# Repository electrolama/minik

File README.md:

# minik

A tiny RP2040 module for small embedded things!

minik is designed by Electrolama / @omerk and licensed under the Solderpad Hardware License 2.0.

## Status

module design files are already in this repo, breakout and libraries to follow. [Here's a preview](https://twitter.com/OmerK/status/1535297431444791298) of what the module and breakout looks like.

## CircuitPython support

minik is supported by CircuitPython! Grab the latest builds [here](https://adafruit-circuit-python.s3.amazonaws.com/index.html?prefix=bin/electrolama_minik).

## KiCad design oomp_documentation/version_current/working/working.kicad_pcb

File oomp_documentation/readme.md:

# None

## Description
None/
## Bill of Materials
| Id | Designator | Footprint | Quantity | Designation | Supplier and ref |  |
| --- | --- | --- | --- | --- | --- | --- |
| 1 | C4,C113,C108,C107,C1<br>09,C112,C114,C105,C1<br>11,C110,C2,C104 | _PKG_C_0402 | 12 | 100n |  |  |
| 2 | R101,R105 | _PKG_R_0402 | 2 | 10k |  |  |
| 3 | R104,R106 | _PKG_R_0402 | 2 | 1k |  |  |
| 4 | C3 | _PKG_C_0402 | 1 | 10u |  |  |
| 5 | C106,C103 | _PKG_C_0402 | 2 | 1u |  |  |
| 6 | R102,R103 | _PKG_R_0402 | 2 | 27 |  |  |
| 7 | LED1 | WS2812B-2020 | 1 | WS2812B-2020 |  |  |
| 8 | C102,C101 | _PKG_C_0402 | 2 | 12p |  |  |
| 9 | IC101 | QFN-56 | 1 | RP2040 |  |  |
| 10 | C1 | _PKG_C_0402 | 1 | 10n |  |  |
| 11 | IC102 | SON50P300X200X60-9N | 1 | MEMORY-W25Q16FWUXIE |  |  |
| 12 | XT101 | XTAL-4P-3225 | 1 | 12MHz |  |  |
| 13 | L1 | _PKG_L_0402 | 1 |  |  |  |

## Images

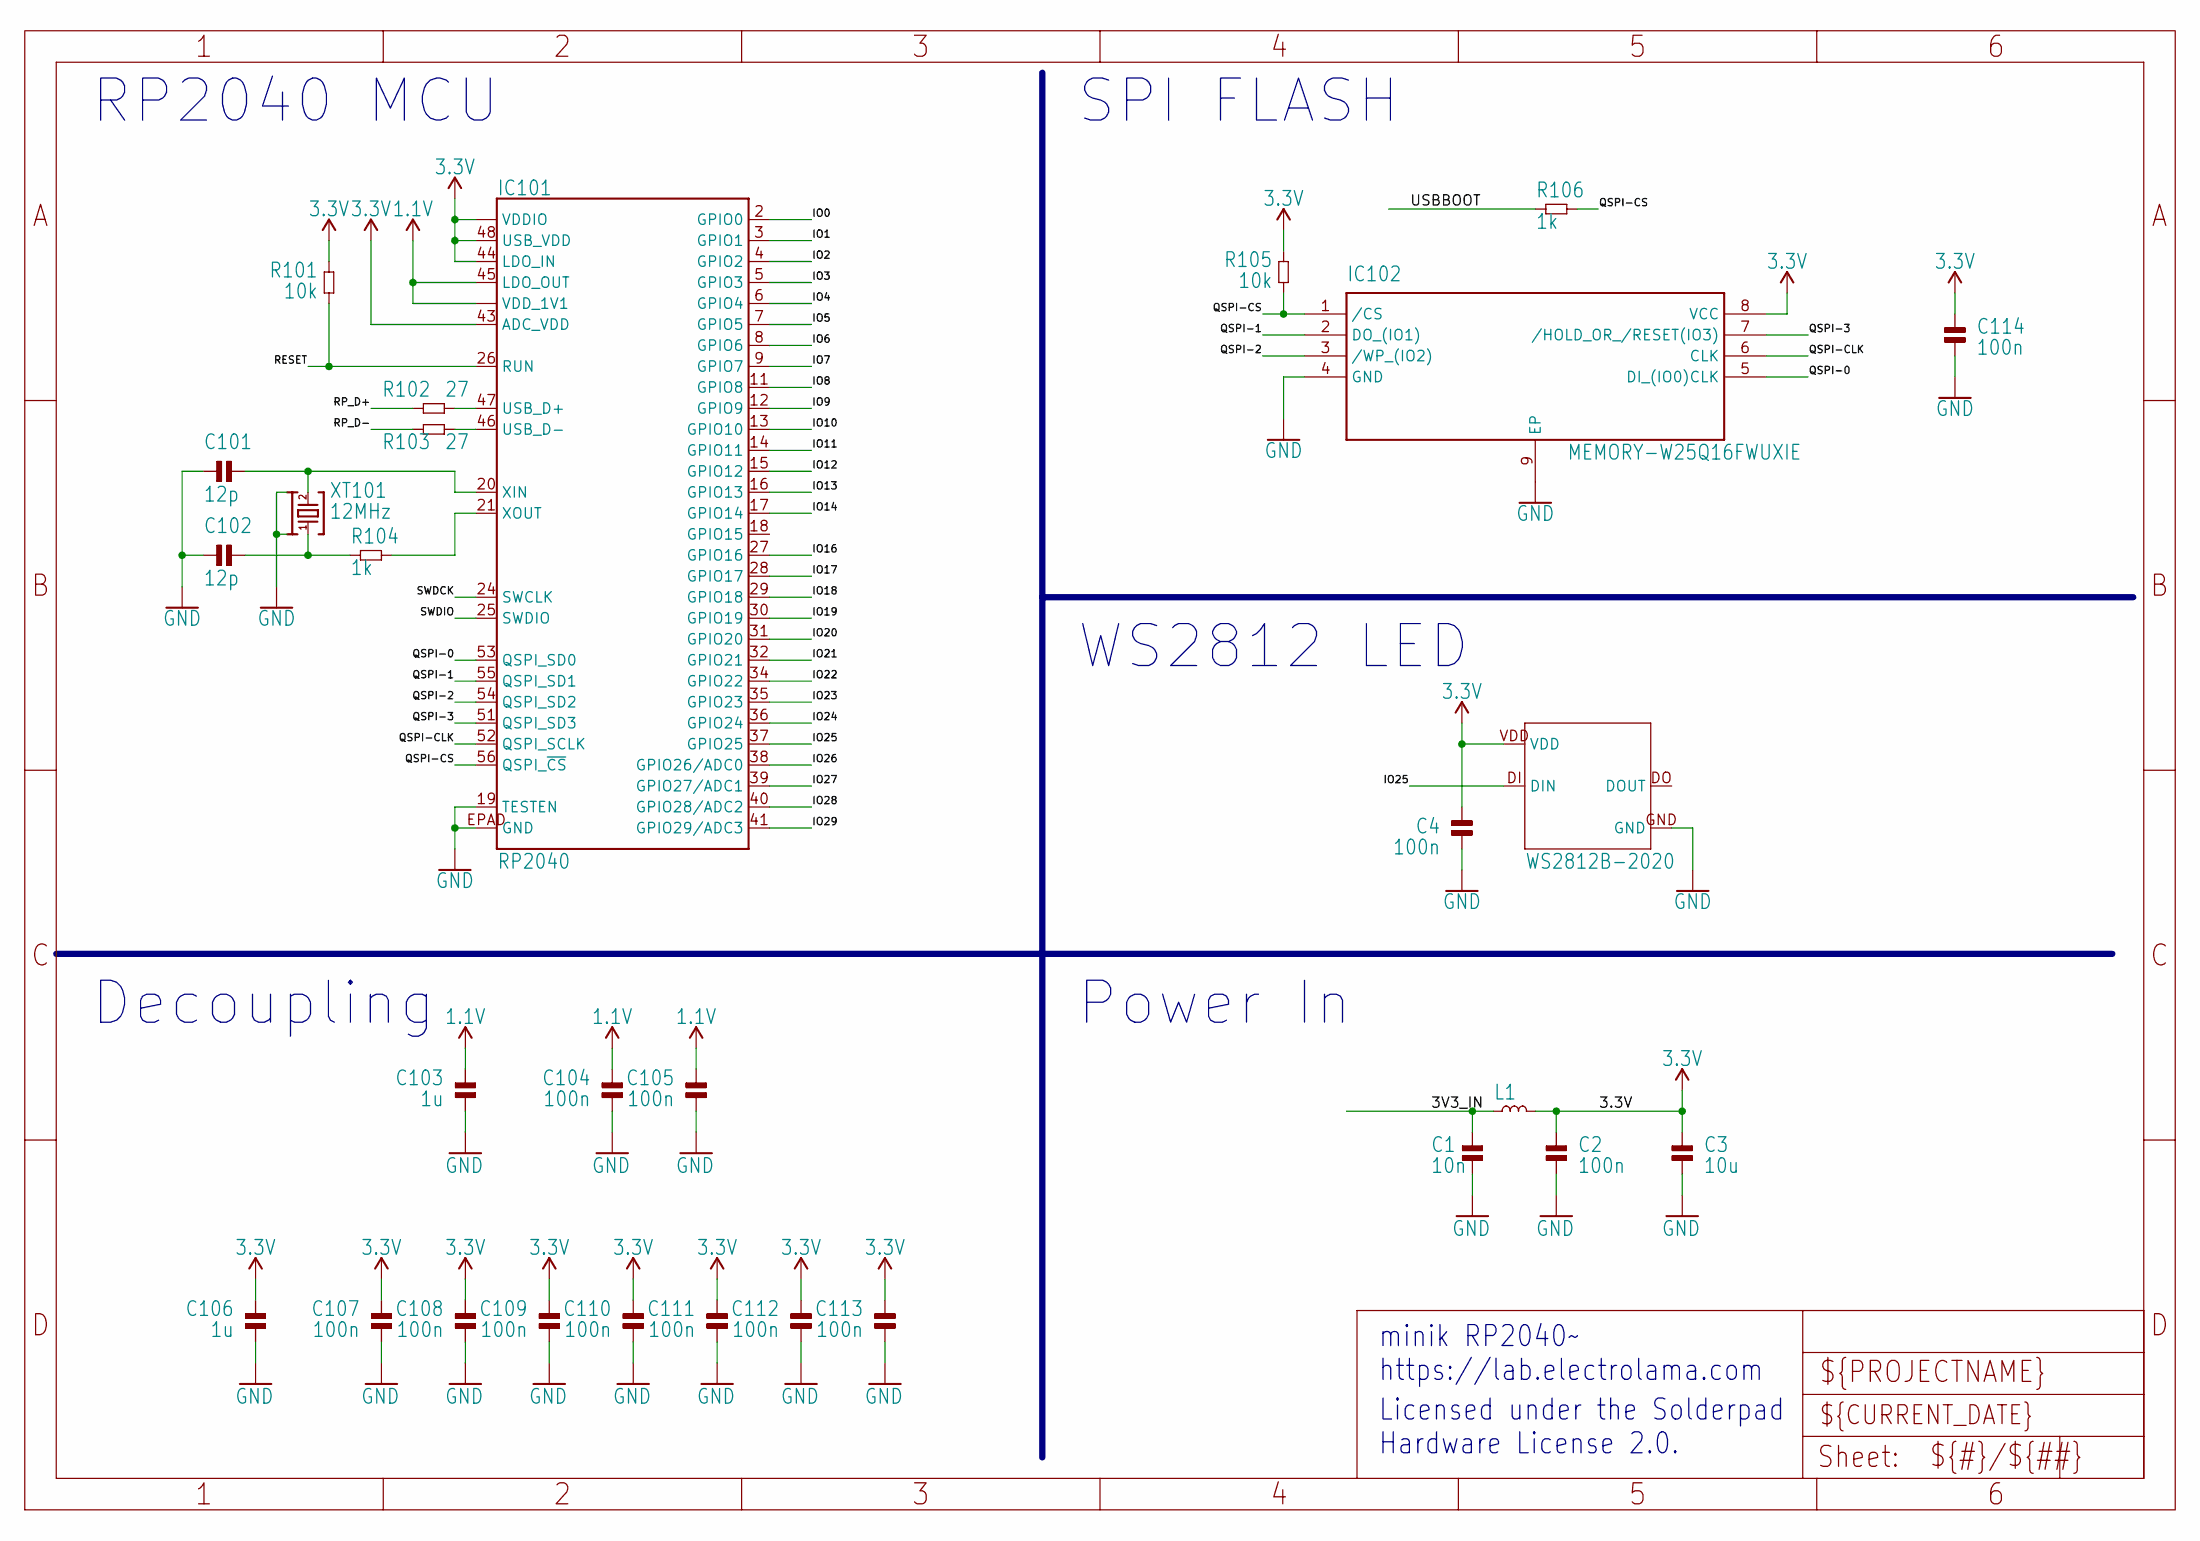
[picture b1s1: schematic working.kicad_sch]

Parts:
C1: 10n; _PKG_C_0402
C2, C4, C104, C105, C107, C108, C109, C110, C111, C112, C113, C114: 100n; _PKG_C_0402
C3: 10u; _PKG_C_0402
C101, C102: 12p; _PKG_C_0402
C103, C106: 1u; _PKG_C_0402
IC101: RP2040; QFN-56
IC102: MEMORY-W25Q16FWUXIE; SON50P300X200X60-9N
L1: INDUCTOR-0402; _PKG_L_0402
LED1: WS2812B-2020
R101, R105: 10k; _PKG_R_0402
R102, R103: 27; _PKG_R_0402
R104, R106: 1k; _PKG_R_0402
XT101: 12MHz; XTAL-4P-3225

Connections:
1.1V: C103.2, C104.2, C105.2, IC101.23 (VDD_1V1), IC101.45 (LDO_OUT), IC101.50 (VDD_1V1)
3.3V: C2.2, C3.2, C4.2, C106.2, C107.2, C108.2, C109.2, C110.2, C111.2, C112.2, C113.2, C114.2, IC101.1 (VDDIO), IC101.10 (VDDIO), IC101.22 (VDDIO), IC101.33 (VDDIO), IC101.42 (VDDIO), IC101.43 (ADC_VDD), IC101.44 (LDO_IN), IC101.48 (USB_VDD), IC101.49 (VDDIO), IC102.8 (VCC), L1.2, LED1.VDD, R101.2, R105.2
3V3_IN: C1.2, L1.1
GND: C1.1, C2.1, C3.1, C4.1, C101.1, C102.1, C103.1, C104.1, C105.1, C106.1, C107.1, C108.1, C109.1, C110.1, C111.1, C112.1, C113.1, C114.1, IC101.19 (TESTEN), IC101.EPAD (GND), IC102.4 (GND), IC102.9 (EP), LED1.GND, XT101.2, XT101.4
IO0: IC101.2 (GPIO0)
IO1: IC101.3 (GPIO1)
IO2: IC101.4 (GPIO2)
IO3: IC101.5 (GPIO3)
IO4: IC101.6 (GPIO4)
IO5: IC101.7 (GPIO5)
IO6: IC101.8 (GPIO6)
IO7: IC101.9 (GPIO7)
IO8: IC101.11 (GPIO8)
IO9: IC101.12 (GPIO9)
IO10: IC101.13 (GPIO10)
IO11: IC101.14 (GPIO11)
IO12: IC101.15 (GPIO12)
IO13: IC101.16 (GPIO13)
IO14: IC101.17 (GPIO14)
IO16: IC101.27 (GPIO16)
IO17: IC101.28 (GPIO17)
IO18: IC101.29 (GPIO18)
IO19: IC101.30 (GPIO19)
IO20: IC101.31 (GPIO20)
IO21: IC101.32 (GPIO21)
IO22: IC101.34 (GPIO22)
IO23: IC101.35 (GPIO23)
IO24: IC101.36 (GPIO24)
IO25: IC101.37 (GPIO25), LED1.DI (DIN)
IO26: IC101.38 (GPIO26/ADC0)
IO27: IC101.39 (GPIO27/ADC1)
IO28: IC101.40 (GPIO28/ADC2)
IO29: IC101.41 (GPIO29/ADC3)
unnamed: IC101.47 (USB_D+), R102.2
unnamed: IC101.46 (USB_D-), R103.2
QSPI-0: IC101.53 (QSPI_SD0), IC102.5 (DI_(IO0)CLK)
QSPI-1: IC101.55 (QSPI_SD1), IC102.2 (DO_(IO1))
QSPI-2: IC101.54 (QSPI_SD2), IC102.3 (/WP_(IO2))
QSPI-3: IC101.51 (QSPI_SD3), IC102.7 (/HOLD_OR_/RESET(IO3))
QSPI-CLK: IC101.52 (QSPI_SCLK), IC102.6 (CLK)
QSPI-CS: IC101.56 (QSPI_~CS), IC102.1 (/CS), R105.1, R106.1
RESET: IC101.26 (RUN), R101.1
RP_D+: R102.1
RP_D-: R103.1
SWDCK: IC101.24 (SWCLK)
SWDIO: IC101.25 (SWDIO)
USBBOOT: R106.2
X1A: IC101.21 (XOUT), R104.2
X1B: C102.2, R104.1, XT101.1
X2: C101.2, IC101.20 (XIN), XT101.3

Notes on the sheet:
Licensed under the Solderpad Hardware License 2.0.
Power In
Decoupling
RP2040 MCU
WS2812 LED
minik RP2040~ https://lab.electrolama.com
SPI FLASH

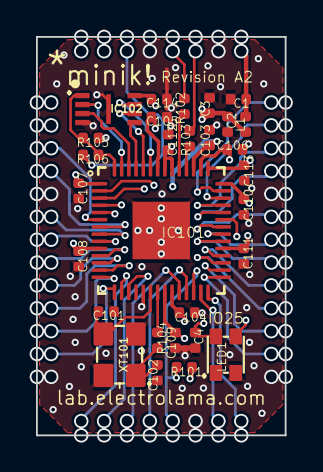
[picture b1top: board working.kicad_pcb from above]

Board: 4 copper layers, 13.8 x 22.1 mm, 29 parts (0 on the bottom side), 17 nets.

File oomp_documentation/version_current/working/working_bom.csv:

"Id";"Designator";"Footprint";"Quantity";"Designation";"Supplier and ref";
1;"C4,C113,C108,C107,C109,C112,C114,C105,C111,C110,C2,C104";"_PKG_C_0402";12;"100n";;;
2;"R101,R105";"_PKG_R_0402";2;"10k";;;
3;"R104,R106";"_PKG_R_0402";2;"1k";;;
4;"C3";"_PKG_C_0402";1;"10u";;;
5;"C106,C103";"_PKG_C_0402";2;"1u";;;
6;"R102,R103";"_PKG_R_0402";2;"27";;;
7;"LED1";"WS2812B-2020";1;"WS2812B-2020";;;
8;"C102,C101";"_PKG_C_0402";2;"12p";;;
9;"IC101";"QFN-56";1;"RP2040";;;
10;"C1";"_PKG_C_0402";1;"10n";;;
11;"IC102";"SON50P300X200X60-9N";1;"MEMORY-W25Q16FWUXIE";;;
12;"XT101";"XTAL-4P-3225";1;"12MHz";;;
13;"L1";"_PKG_L_0402";1;"";;;

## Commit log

2022-06-12 minik module RevA2 sources and schematics PDF
2022-06-12 minik module RevA2 production files
2022-06-15 update status and preliminary circuitpython info
2022-06-20 update circuitpython info
2023-07-23 oomp_documentation added
2023-07-23 proper oomp_documentation
2023-07-23 fixed readme
